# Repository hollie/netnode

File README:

This is the repository for the netnode project. 

WHAT IS THIS?
-------------

The netnode is an Ethernet-connected microcontroller. It is designed as a generic electronics platform that can be used to automate various tasks in and around the house.

The first version is built around a Microchip PIC microcontroller and a LanTronix XPORT serial to Ethernet convertor.

In this form, the netnode is running for over 5 years at our home. It is used to control electrical blinds, to measure temperatures in our HVAC system, to monitor our solar heating installation, to measure the output of a photovoltaic installation and to interface to wireless sensors.

The latest developments around the netnode focus on adding a standard interface for reporting sensors data and to control basic devices. The selected standard is xPL, because it allows coupling the netnode to a vast amount of existing software such as e.g. Misterhouse.

This repository is divided in three sections: 
 * hardware: the hardware design files of the netnode. The netnode is designed in Eagle and the design is open source (see license below).
 * firmware: the firmware for the controller on the netnode. Currently there is only a single subfolder here. All existing firmware is mapped on a netnode v1.x that is based on a Microchip PIC18F controller.
 * software: various host software packages used to interface to a netnode running a certain firmware. Most of the subfolders here implement a kind of datalogging functionality to RRD databases.
    
AUTHOR
------

Lieven Hollevoet designed the netnode at the time he was building his house. His goal was to build a low-energy home, and setting such a goal of course implies deploying a measurement network to check if the efforts were worthwhile. 
After experimenting with a CAN-based solution, he decided Ethernet was the way to go. The main reasons to go for Ethernet were that the cabling was already present, and that on the computer interface side Ethernet is an interface that is available on every computing device, opposed to CAN which isn't. 

CREDITS
-------

Some 'like-minded' people have contributed to the codebase. 

Dirk Buekenhoudt helped in coding and debugging the xPL interface code. He is currently working on adding digital inputs and outputs.

Roeland Vandebriel wrote the initial code for the SHT7x humidity sensors and is working on merging my Technische Alternative DL output interface code that I initially wrote for my TA UVR61-1. He is working on interfacing to the TA UVR1611.

DEMO
----

A demo of what measurements are done using netnode hardware can be found here:
http://lika.be/uushuus_stats/live.htm

LICENSE
-------

All work in this repository is available under the Creative Commons 
Attribution-NonCommercial-ShareAlike license 3.0.

http://creativecommons.org/licenses/by-nc-sa/3.0/

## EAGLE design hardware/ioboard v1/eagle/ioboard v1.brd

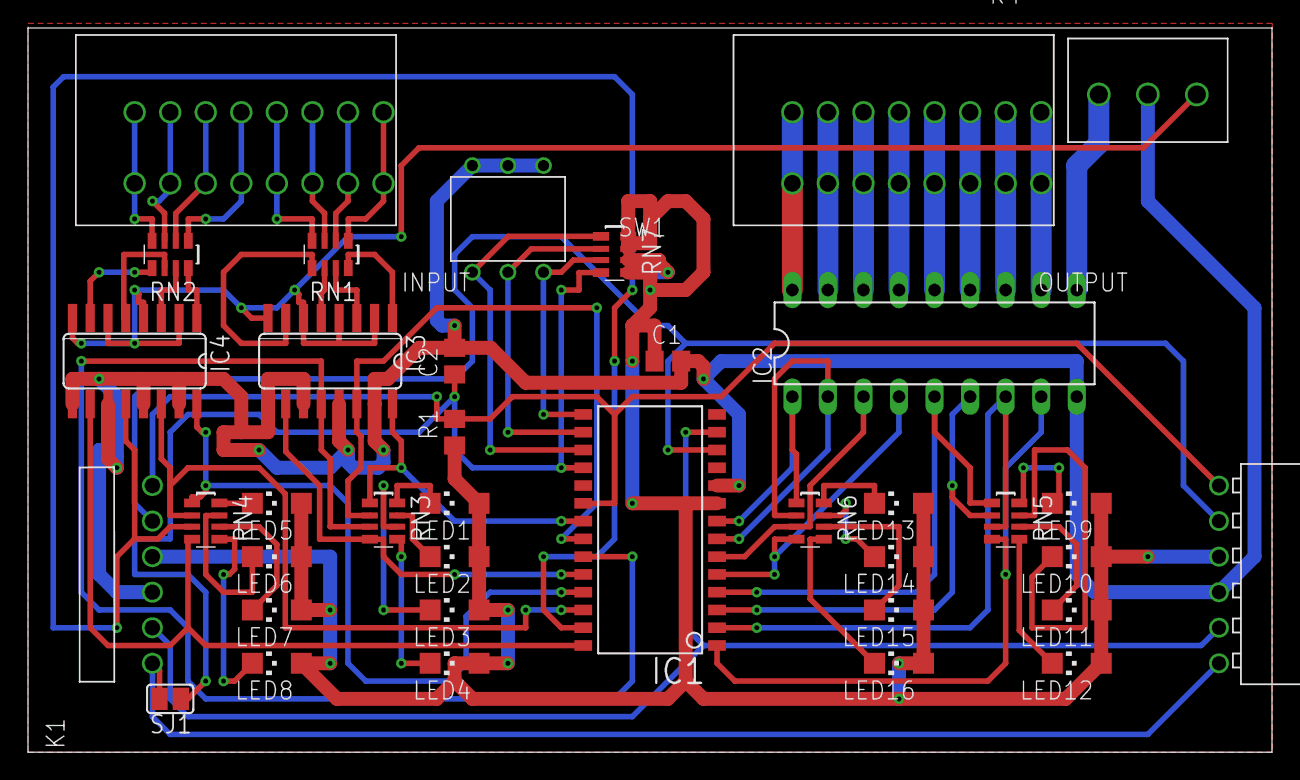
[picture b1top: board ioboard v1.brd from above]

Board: 2 copper layers, 88.9 x 51.7 mm, 37 parts (0 on the bottom side), 68 nets.

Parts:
C1, C2: C0805
IC1: MCP23017SO; SO28W
IC2: DIL18
IC3, IC4: ACPL-244; SO16
INPUT: 691402910008
K1: 61300611021
K2: 613006143121
K4: 691214110003
LED1, LED2, LED3, LED4, LED5, LED6, LED7, LED8, LED9, LED10, LED11, LED12, LED13, LED14, LED15, LED16: CHIPLED_1206
OUTPUT: 691402910008
R1: R0805
RN1, RN2, RN3, RN4, RN5, RN6, RN7: RN8P-4R-CRA06S
SJ1: SJ
SW1: 418127270903

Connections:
!RST: C2.1, IC1.18, RN7.4, SJ1.1
ADDR0: IC1.15, RN7.3, SW1.6
ADDR1: IC1.16, RN7.2, SW1.5
ADDR2: IC1.17, RN7.1, SW1.4
AGND: IC3.2, IC3.4, IC3.6, IC3.8, IC4.2, IC4.4, IC4.6, IC4.8, K4.3
GND: C1.2, C2.2, IC1.10, IC2.9, IC3.9, IC3.11, IC3.13, IC3.15, IC4.9, IC4.11, IC4.13, IC4.15, K1.4, K2.4, K4.2, SW1.1, SW1.2, SW1.3
IN0: INPUT.1, INPUT.16, RN1.1
IN1: INPUT.2, INPUT.15, RN1.2
IN2: INPUT.3, INPUT.14, RN1.3
IN3: INPUT.4, INPUT.13, RN1.4
IN4: INPUT.5, INPUT.12, RN2.1
IN5: INPUT.6, INPUT.11, RN2.2
IN6: INPUT.7, INPUT.10, RN2.3
IN7: INPUT.8, INPUT.9, RN2.4
INT: IC1.20, K1.1, K2.1, R1.2
IN_L0: IC1.21, IC3.16, RN3.1
IN_L1: IC1.22, IC3.14, RN3.2
IN_L2: IC1.23, IC3.12, RN3.3
IN_L3: IC1.24, IC3.10, RN3.4
IN_L4: IC1.25, IC4.16, RN4.1
IN_L5: IC1.26, IC4.14, RN4.2
IN_L6: IC1.27, IC4.12, RN4.3
IN_L7: IC1.28, IC4.10, RN4.4
unnamed: IC3.1, RN1.8
unnamed: IC3.3, RN1.7
unnamed: IC3.5, RN1.6
unnamed: IC3.7, RN1.5
unnamed: IC4.1, RN2.8
unnamed: IC4.3, RN2.7
unnamed: IC4.5, RN2.6
unnamed: IC4.7, RN2.5
unnamed: LED1.C, RN3.8
unnamed: LED2.C, RN3.7
unnamed: LED9.C, RN5.8
unnamed: LED10.C, RN5.7
unnamed: LED11.C, RN5.6
unnamed: LED12.C, RN5.5
unnamed: LED3.C, RN3.6
unnamed: LED4.C, RN3.5
unnamed: LED13.C, RN6.8
unnamed: LED14.C, RN6.7
unnamed: LED15.C, RN6.6
unnamed: LED16.C, RN6.5
unnamed: LED5.C, RN4.8
unnamed: LED6.C, RN4.7
unnamed: LED7.C, RN4.6
unnamed: LED8.C, RN4.5
OUT0: IC2.11, OUTPUT.1, OUTPUT.16
OUT1: IC2.12, OUTPUT.2, OUTPUT.15
OUT2: IC2.13, OUTPUT.3, OUTPUT.14
OUT3: IC2.14, OUTPUT.4, OUTPUT.13
OUT4: IC2.15, OUTPUT.5, OUTPUT.12
OUT5: IC2.16, OUTPUT.6, OUTPUT.11
OUT6: IC2.17, OUTPUT.7, OUTPUT.10
OUT7: IC2.18, OUTPUT.8, OUTPUT.9
OUT_L0: IC1.1, IC2.8, RN5.4
OUT_L1: IC1.2, IC2.7, RN5.3
OUT_L2: IC1.3, IC2.6, RN5.2
OUT_L3: IC1.4, IC2.5, RN5.1
OUT_L4: IC1.5, IC2.4, RN6.4
OUT_L5: IC1.6, IC2.3, RN6.3
OUT_L6: IC1.7, IC2.2, RN6.2
OUT_L7: IC1.8, IC2.1, RN6.1
RST_EXT: K1.6, K2.6, SJ1.2
SCL: IC1.12, K1.2, K2.2
SDA: IC1.13, K1.5, K2.5
V+: IC2.10, K4.1
VDD: C1.1, IC1.9, K1.3, K2.3, LED1.A, LED2.A, LED3.A, LED4.A, LED5.A, LED6.A, LED7.A, LED8.A, LED9.A, LED10.A, LED11.A, LED12.A, LED13.A, LED14.A, LED15.A, LED16.A, R1.1, RN7.5, RN7.6, RN7.7, RN7.8

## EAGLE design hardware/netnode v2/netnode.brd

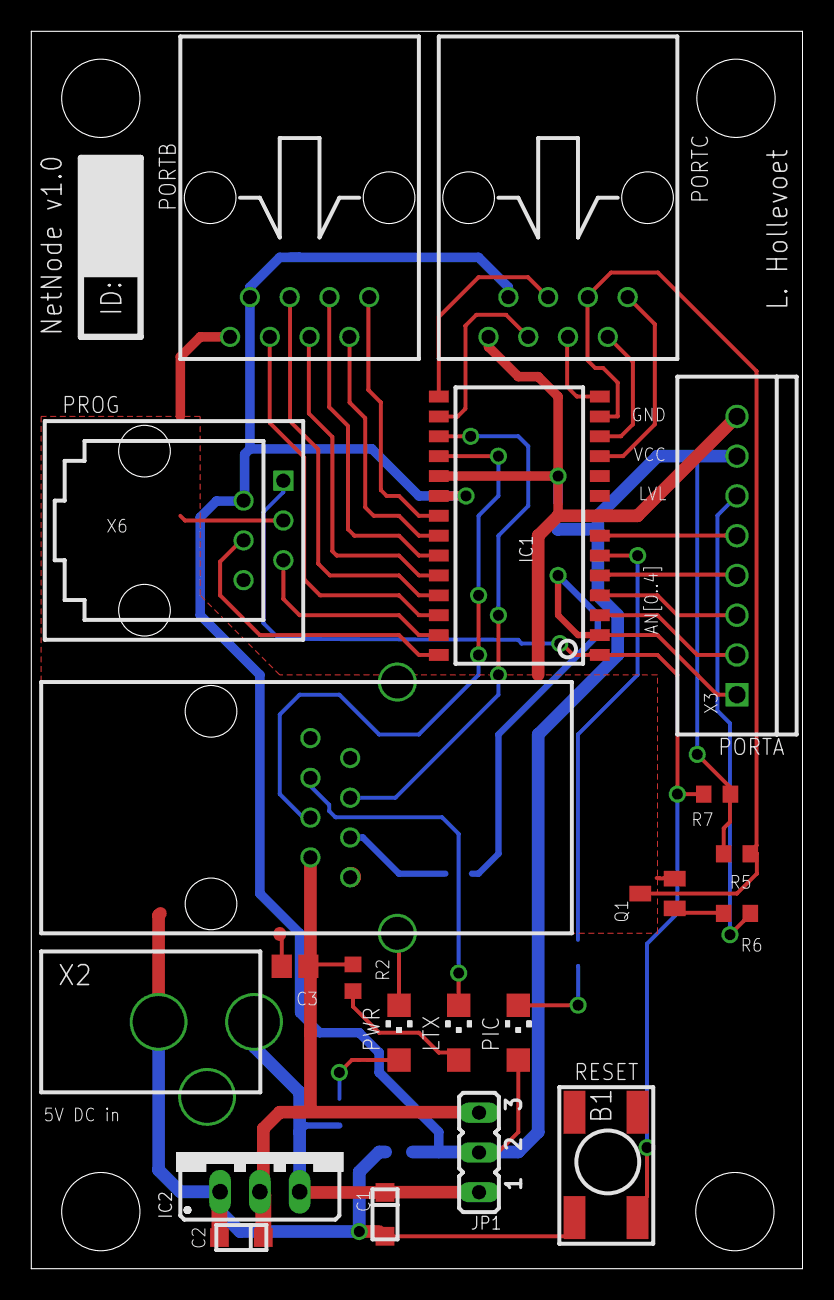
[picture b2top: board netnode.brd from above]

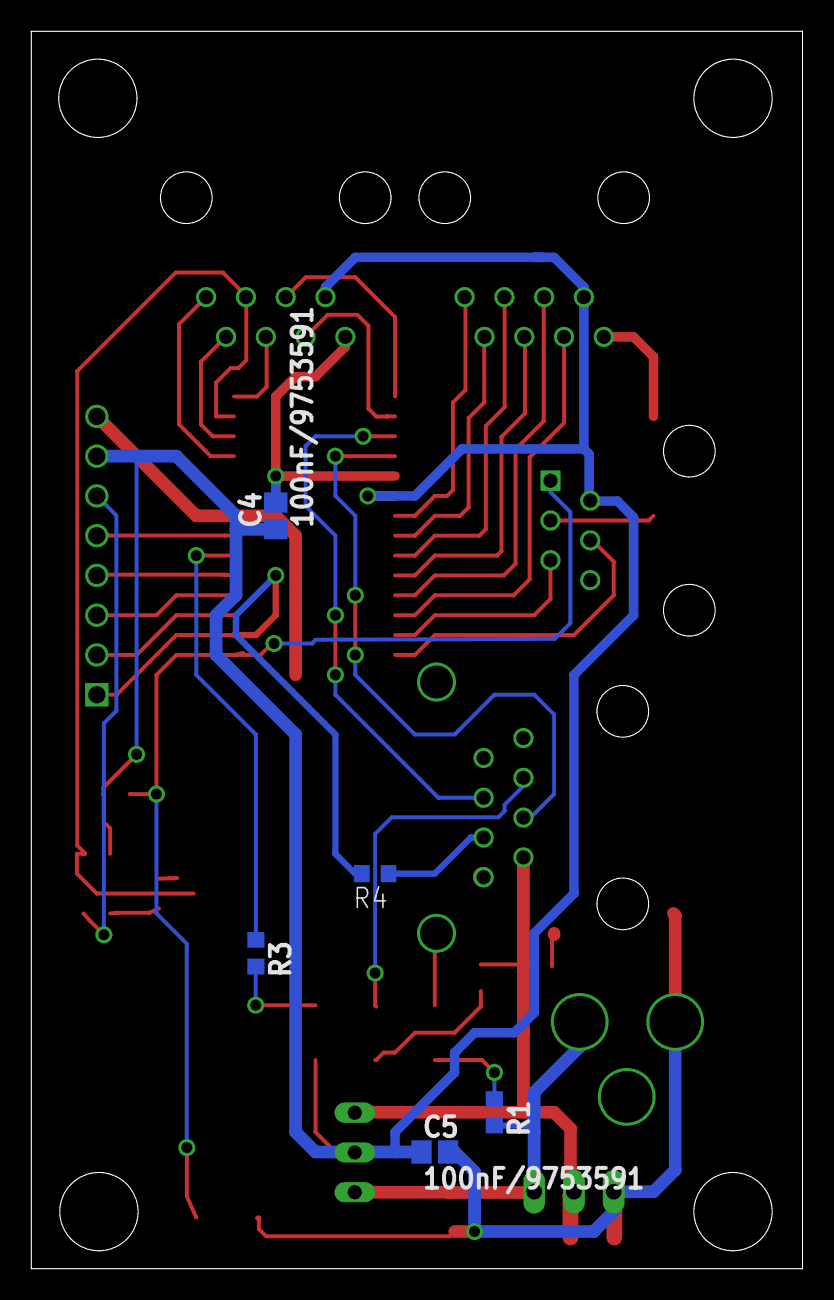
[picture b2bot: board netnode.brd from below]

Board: 4 copper layers, 49.3 x 79.0 mm, 26 parts (5 on the bottom side), 34 nets.

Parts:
B1: 9902031; PUSHBUTTON
C1, C2: 10u/7565127; CHIPCAP
C3, C4, C5: 100nF/9753591; C0805
IC1: PIC18F2320/9762051; SO-28W
IC2: 1087165; 78XXS
JP1: JP2
LTX: CHIPLED_1206
PIC: CHIPLED_1206
PWR: CHIPLED_1206
Q1: 1081235; SOT23
R1, R2, R3: R0603
R4: 0; R0603
R5: 10k/9331700; R0603
R6: 470k/612807RL; R0603
R7: 1k/9331697RL; R0603
X1: XPORT
X2: DC10R/224959; DC10R
X3: SCREW_TERMINAL/3041438; SCREW_TERMINAL_8PINS
X4, X5: RJ45H
X6: X/1097917; RJ11

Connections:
+3V3: C2.+, C3.1, IC2.GND, JP1.3, R2.2, X1.2
+5V: C1.+, IC2.OUT, JP1.1, R1.2, X2.1
AN0: IC1.2, R4.2, X3.1
AN1: IC1.3, X3.2
AN2: IC1.4, X3.3
AN3: IC1.5, X3.4
AN4: IC1.7, X3.5
CP1: LTX.C, X1.6
GND: B1.1, C1.-, C2.-, C3.2, C4.2, C5.2, IC1.8, IC1.19, IC2.IN, PWR.C, Q1.2, X1.1, X1.TAB1, X1.TAB2, X2.3, X3.8, X4.P$8, X5.P$8, X6.3
LVL: R6.2, X3.6
MCLR: B1.3, IC1.1, R7.2, X6.1
unnamed: Q1.1, R6.1
unnamed: PWR.A, R1.1
unnamed: R4.1, X1.3
unnamed: LTX.A, R2.1
PIC: PIC.C, R3.2
PIC_RX: IC1.18, X1.4
PIC_TX: IC1.17, X1.5
RA4: IC1.6, R3.1
RB0: IC1.21, X4.P$1
RB1: IC1.22, X4.P$2
RB2: IC1.23, X4.P$3
RB3: IC1.24, X4.P$4
RB4: IC1.25, X4.P$5
RB5: IC1.26, X4.P$6
RB6: IC1.27, X6.5
RB7: IC1.28, X6.4
RC0: IC1.11, X5.P$1
RC1: IC1.12, X5.P$2
RC2: IC1.13, Q1.3, R5.1, X5.P$3
RC3: IC1.14, X5.P$4
RC4: IC1.15, X5.P$5
RC5: IC1.16, X5.P$6
VCC: C4.1, C5.1, IC1.20, JP1.2, PIC.A, R5.2, R7.1, X3.7, X4.P$7, X5.P$7, X6.2

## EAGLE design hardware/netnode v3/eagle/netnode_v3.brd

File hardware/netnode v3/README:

Specifications of the Netnode v3
================================

Ethernet-connected PIC microcontroller

Highlights:
-----------
* Input voltage: 5 - 30 V, short circuit protected
* 10/100 Ethernet connection configurable through web interface on port 80
* System voltage: 3V3
* Can deliver up to 600 mA to target application.
* Typical power consumption: 0.92 W with ethernet running in normal performance mode
* 8-pin screw terminal connector with 4 GPIOs + ground connected to interrupt pins
* 8-pin screw terminal connector with I2C, 1 PWM, 1 optically isolated input, 1 one-wire bus, 3V3 and GND 
* 4 analog input pins broken out to non-populated header
* ICSP header on board
* Second serial port broken out to header to be able to easily connect XBee radio modules
* PIC has bootloader that allows firmware upgrades over the ethernet interface (*)
* optically isolated input designed for 12V input level (level can be changed by replacing a resistor)
* Open hardware, you're invited to thinker with it. 

Description:
------------
This is a PIC board that was developed to monitor the energy consumption and temperatures in and around our house. Multiple firmwares are available that can be loaded to have the board perform the functionality that is required.

Available firmwares are:
------------------------
 * one-wire to xPL bridge. Allows connecting one-wire temperature sensors, reports their status over xPL for easy integration with existing xPL software (e.g. Misterhouse). Plug the device in your network and the sensors appear in the software.
 * one-wire and SHTxx relative humidity to Cosm bridge. Idem as previous, but reports the sensor status to Cosm.com (previously Pachube). Ideal for people that don't have or want to keep a home server running to report sensor values to Cosm.
 * Technische Alternative solar heating controller interface (TA UVR61-3 and alike). Reports the status of your controller and the attached sensors over xPL (*).
 * TA to Cosm bridge. Idem as previous but reports to Cosm.com instead (*).

*: to be implemented

All work in this folder is available under the Creative Commons 
Attribution-NonCommercial-ShareAlike license 3.0.

http://creativecommons.org/licenses/by-nc-sa/3.0/

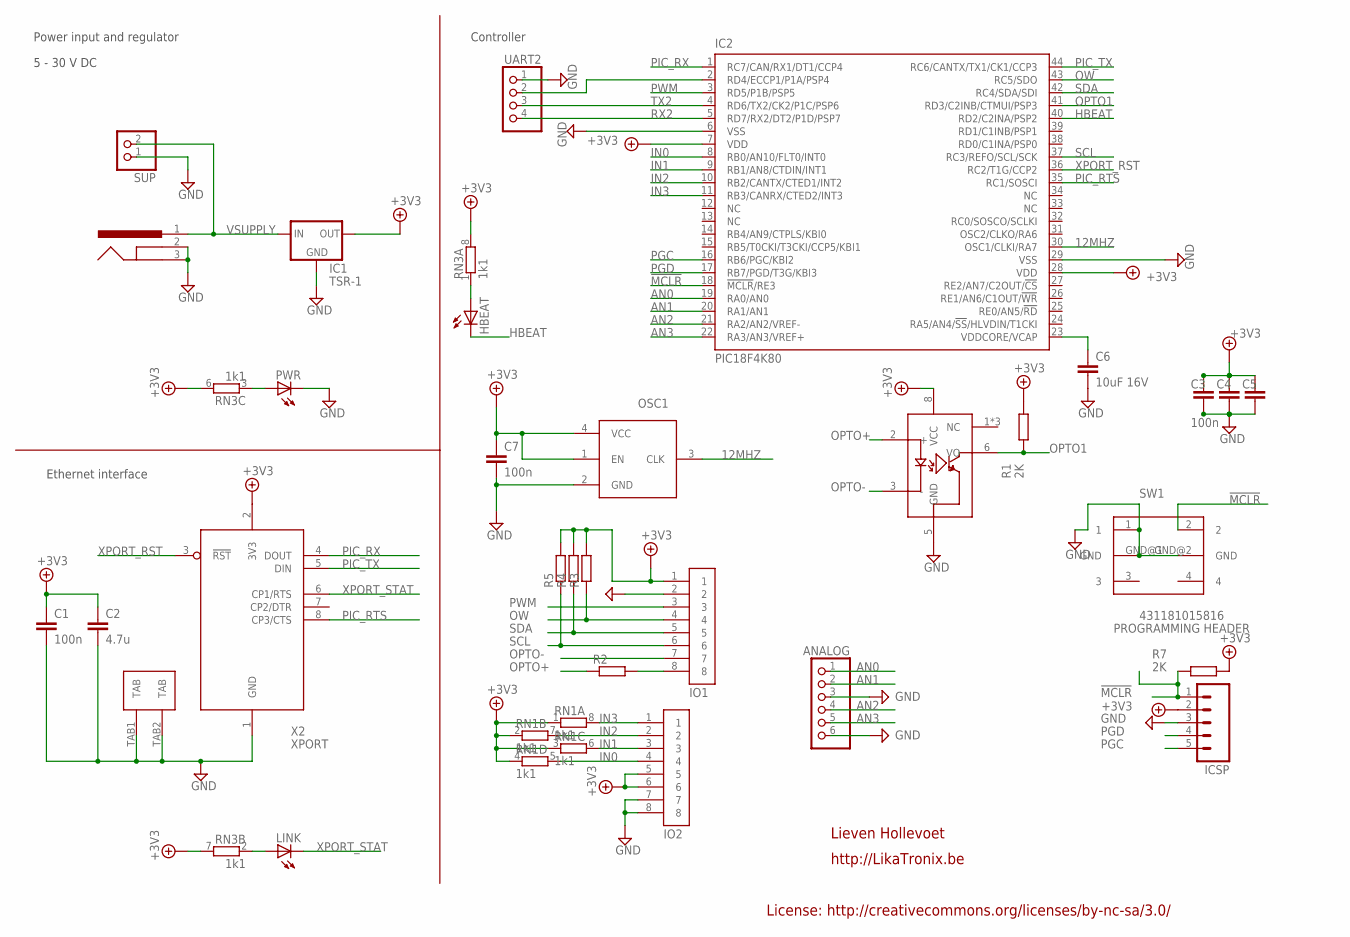
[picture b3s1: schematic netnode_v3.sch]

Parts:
ANALOG: PINHD-1X6; 1X06
C1, C3, C4, C5, C7: 100n; C0805; MPN 08055C104JAT2A
C2: 4.7u; C0805; MPN 0805YD475KAT2A
C6: 10uF 16V; C1206; MPN C1206C106K4PAC-TU
HBEAT: LEDCHIPLED_1206; CHIPLED_1206; MPN KP-3216EC
IC1: TSR-1; TSR1-SIPS; MPN TSR 1-2433
IC2: PIC18F4K80; TQFP44; MPN PIC18F45K80-I/PT
IC3: FOD060L; SO-08
ICSP: ICSP; 1X05
IO1, IO2: SCREW_TERMINAL; SCREW_TERMINAL_8PINS; MPN 1725711
LINK: LEDCHIPLED_1206; CHIPLED_1206; MPN KP-3216EC
OSC1: TXC - 7X-12.000MBB-T; 7W_7X5; MPN 7X-12.000MBB-T
PWR: LEDCHIPLED_1206; CHIPLED_1206; MPN KP-3216EC
R1, R7: 2K; R0805; MPN CR0603-FX-2001ELF
R2: R-EU_M0805; M0805
R3, R4, R5: R-EU_R0603; R0603
RN1, RN3: 1k1; RN8P-4R-CRA06S; MPN EXB38V102JV
SUP: PINHD-1X2; 1X02
SW1: 431181015816
UART2: PINHD-1X4; 1X04
X1: DC10R; MPN DC10A
X2: XPORT

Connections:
12MHZ: IC2.30 (OSC1/CLKI/RA7), OSC1.3 (CLK)
!MCLR: IC2.18 (!MCLR!/RE3), ICSP.1, R7.1, SW1.2
+3V3: C1.1, C2.1, C3.1, C4.1, C5.1, C7.1, IC1.3 (OUT), IC2.7 (VDD), IC2.28 (VDD), IC3.8 (VCC), ICSP.2, IO1.1, IO2.5, IO2.6, OSC1.1 (EN), OSC1.4 (VCC), R1.2, R3.2, R4.2, R5.2, R7.2, RN1.1, RN1.2 (1), RN1.3 (1), RN1.4 (1), RN3.6 (2), RN3.7 (2), RN3.8 (2), X2.2 (3V3)
AN0: ANALOG.1, IC2.19 (RA0/AN0)
AN1: ANALOG.2, IC2.20 (RA1/AN1)
AN2: ANALOG.4, IC2.21 (RA2/AN2/VREF-)
AN3: ANALOG.5, IC2.22 (RA3/AN3/VREF+)
GND: ANALOG.3, ANALOG.6, C1.2, C2.2, C3.2, C4.2, C5.2, C6.2, C7.2, IC1.2 (GND), IC2.6 (VSS), IC2.29 (VSS), IC3.5 (GND), ICSP.3, IO1.2, IO2.7, IO2.8, OSC1.2 (GND), PWR.C, SUP.1, SW1.1, SW1.GND@1 (GND), SW1.GND@2 (GND), UART2.1, X1.2 (CONTACT), X1.3 (SHIELD), X2.1 (GND), X2.TAB1 (TAB), X2.TAB2 (TAB)
HBEAT: HBEAT.C, IC2.40 (RD2/C2INA/PSP2)
IN0: IC2.8 (RB0/AN10/FLT0/INT0), IO2.4, RN1.5 (2)
IN1: IC2.9 (RB1/AN8/CTDIN/INT1), IO2.3, RN1.6 (2)
IN2: IC2.10 (RB2/CANTX/CTED1/INT2), IO2.2, RN1.7 (2)
IN3: IC2.11 (RB3/CANRX/CTED2/INT3), IO2.1, RN1.8 (2)
unnamed: LINK.A, RN3.2 (1)
unnamed: PWR.A, RN3.3 (1)
unnamed: HBEAT.A, RN3.1
OPTO1: IC2.41 (RD3/C2INB/CTMUI/PSP3), IC3.6 (VO), R1.1
OPTO+: IC3.2 (+), R2.1
OPTO+_PRE_RES: IO1.8, R2.2
OPTO-: IC3.3 (-), IO1.7
OW: IC2.43 (RC5/SDO), IO1.4, R3.1
PGC: IC2.16 (RB6/PGC/KBI2), ICSP.5
PGD: IC2.17 (RB7/PGD/T3G/KBI3), ICSP.4
PIC_RTS: IC2.35 (RC1/SOSCI), X2.8 (CP3/CTS)
PIC_RX: IC2.1 (RC7/CAN/RX1/DT1/CCP4), X2.4 (DOUT)
PIC_TX: IC2.44 (RC6/CANTX/TX1/CK1/CCP3), X2.5 (DIN)
PWM: IC2.3 (RD5/P1B/PSP5), IO1.3
RD4: IC2.2 (RD4/ECCP1/P1A/PSP4), UART2.2
RX2: IC2.5 (RD7/RX2/DT2/P1D/PSP7), UART2.4
SCL: IC2.37 (RC3/REFO/SCL/SCK), IO1.6, R5.1
SDA: IC2.42 (RC4/SDA/SDI), IO1.5, R4.1
TX2: IC2.4 (RD6/TX2/CK2/P1C/PSP6), UART2.3
VDDCAP: C6.1, IC2.23 (VDDCORE/VCAP)
VSUPPLY: IC1.1 (IN), SUP.2, X1.1 (CENTER)
XPORT_RST: IC2.36 (RC2/T1G/CCP2), X2.3 (!RST)
XPORT_STAT: LINK.C, X2.6 (CP1/RTS)

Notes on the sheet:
Power input and regulator
5 - 30 V DC
Ethernet interface
PROGRAMMING HEADER
Lieven Hollevoet
http://LikaTronix.be
License: http://creativecommons.org/licenses/by-nc-sa/3.0/
Controller

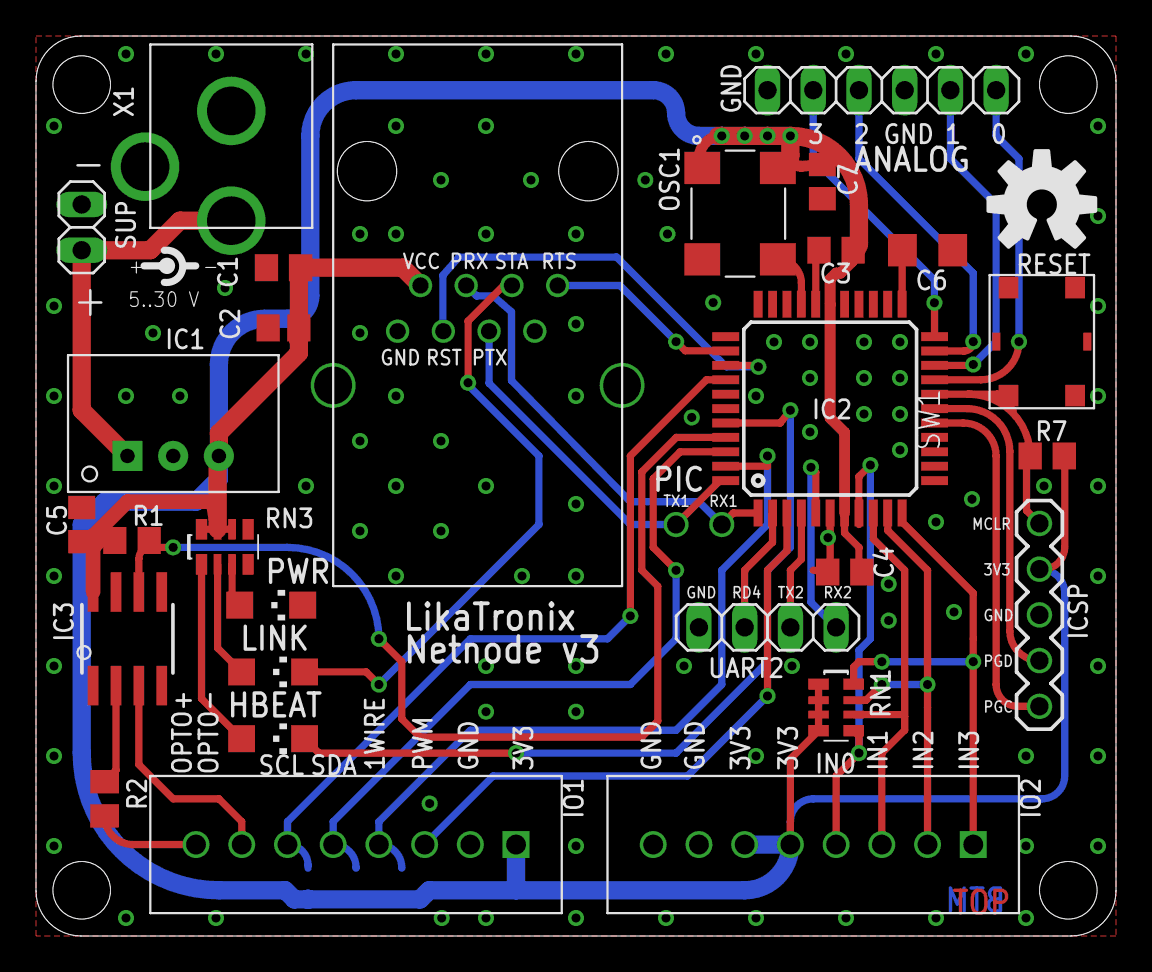
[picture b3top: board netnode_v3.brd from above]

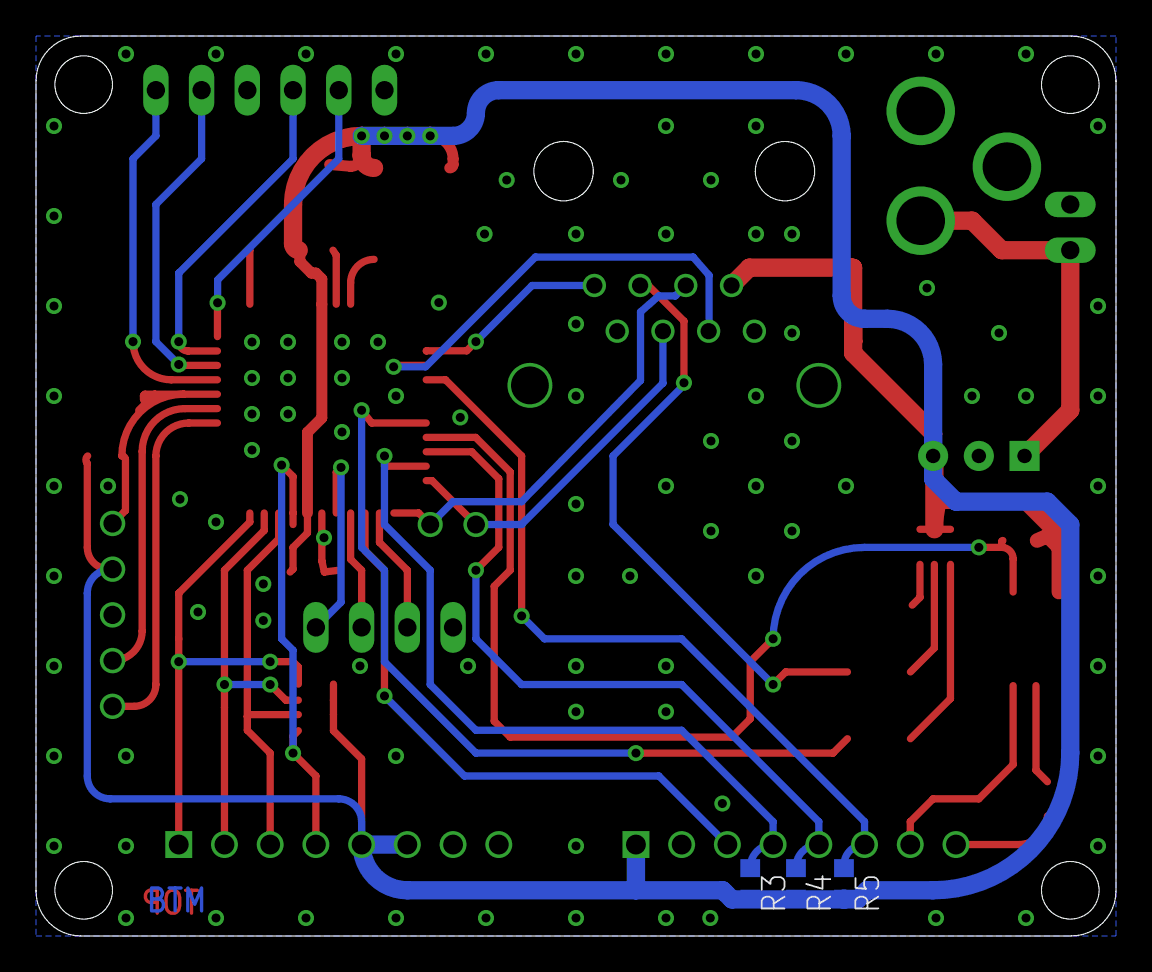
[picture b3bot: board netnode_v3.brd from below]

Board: 2 copper layers, 60.0 x 50.0 mm, 31 parts (3 on the bottom side), 36 nets.

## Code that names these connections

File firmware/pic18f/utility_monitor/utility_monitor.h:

/*************************************************************
* Utility meter monitor
*
* (c) 2009, Lieven Hollevoet.
**************************************************************
* compiler        : Microchip C18 v3.40
* target device   : PIC18F2520/PIC18F2580
* clockfreq       : 8 MHz (internal oscillator)
* target hardware : NetNode
* UART speed      : 38400 bps
*************************************************************/
#ifndef _UTILMONI_H_
#define _UTILMONI_H_

// Define port directions, 1=input
#define PortAConfig  	0xFF
#define PortBConfig  	0x0F
#define PortCConfig  	0xBB
#define PortDConfig     0xF0

// Define bit variables attached to pins
#ifdef __18F45K80_H

#define stat0    (PORTDbits.RD2)
#define xport_rst (PORTCbits.RC2)
#define xport_cts (PORTCbits.RC1)

// Timer values
#define TMR0_VALUE 0x0BDB // For a second interrupt runnning @ 64 MHz with 256 prescaler
#define TMR1_VALUE 0xB1E0 // For 20 ms interrupt.

/* TODO fix the timer values */

#else

#define stat0    (PORTAbits.RA4)

// Timer values
#define TMR0_VALUE 0x85EE // For a second interrupt.
#define TMR1_VALUE 0xB1E0 // For 20 ms interrupt.

#endif

#define show_hbeat() (blink_hbeat += 5);

// Function declarations
void init(void);
void high_isr(void);
void low_isr(void);


#endif //_UTILMONI_H_

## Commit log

2012-03-10 Added firmware for utility monitor
2012-03-10 Updated formatting of the README
2012-03-10 Fixed the compiler warnings caused by different compilation options of the libs vs the code
2012-03-10 Removed error files
2012-03-14 Added support for Sensirion SHTxx humidity sensors.
    Initial support for the sensors is added based on the code migrated by
    Roeland from my PSOC library.
    The readout is working and was reported through a non-standard xPL
    message.
    To be done: add xPL message support conform the specification.
    Bumped the firmware version to v4.6
2012-03-14 Started adding xPL compliant support for the SHT sensor
    Prepared the xPL lib for regularly polling the SHT sensor and to sense
    out xpl-trig messages when the reading changed.
    Bugfix: xpl_node_configuration was mistakingly reset completely in the
    init_instance_id function.
2012-03-15 Added reporting of the SHT sensor readings to the xPL library
2012-03-15 SHT sensor reporting tested on hardware
2012-03-21 Typo fix in README
2012-04-15 Added debug server script
2012-04-15 Added test client, updates test server
2012-04-15 Made client resemble curl.
2012-04-15 Oops, TCP packet should end with \r\n\r\n
2012-05-05 Updated test server for socket client testing
2012-05-05 Added first firmware for the Cosm interface
2012-05-06 Added description.
2012-05-06 Added project description and license.
2012-05-11 Correct calculation of whole and part value's
    For negative numbers the value_whole and value_part where not
    calculated correctly.
2012-05-11 Corrections for the decimals
    If the decimals where 09 or 0 something they where displayed without
    the 0
2012-05-11 correct the caluculation of value_whole and value_part for negative values
2012-05-12 Revert "correct the caluculation of value_whole and value_part for negative values"
    This reverts commit 01e6d6504f04271bffc7768f77fabc0a21840e01.
2012-05-12 - Move FeedNr to gateway - An other fix for negative temp values, when the value < 0 and > -1 eg -0,92 the - sign disapear because -0 does not exist.
2012-05-15 Implement multisensor code
2012-05-15 Added feed id to init function, bug fixed printing of scaled negative values.
2012-05-15 Updated gitignore and fixed a potential case where we miss the reporting condition due to condition not matching (unlikely, but better to be safe than to be sorry).
2012-06-11 Intermediate release, schematic to be completed.
2012-06-11 Backported bugfix fro Roeland
2012-06-15 Pre-final board files, silkscreen to be fixed
2012-06-17 Typo fix
2012-07-09 Further finalization of board
2012-07-09 Added project description
2012-07-16 Completed order codes.
2012-07-16 Added resistors and cleaned silkscreen
2012-07-16 Updated gitignore file to omit object files
2012-07-16 New firmware for PV reporting to Cosm
    Still in alpha phase, to be testen on hardware.
2012-07-16 Added changes to MPlab X files of the libs
2012-07-16 Changes to MPLab X files (new build platform)
2012-07-19 Further board cleanup
    * Silkscreen fixes + size increased
    * Replaced 0603 componentsn with 0805 counterparts for easier soldering
2012-07-19 Intermediate checkin, code to be tested
    In the process of moving the settings to EEPROM
2012-11-03 Added reset button.
    The reset button from Wuerth is a handy addition when developing firmware.
2012-11-11 Final fixes for boardout.
    Added decoupling caps, fixed silkscreen, reviewed compontents
2012-11-11 Added gerbers.
2012-11-11 Final gerber file commit of files sent to production. Fixed problems detected by PCB visualizer.
2012-11-11 Added historical versions of netnode for completeness, added initial version of inboard.
2012-11-14 Intermediate commit of ioboard.
2012-11-17 Updated IOboard with some more connectors and LEDs
2012-11-18 First board layout
2012-11-18 First routing attempt aith autorouter
    But no rules, just to know the routing is possible
2013-01-29 Initial support for v3 hardware
2013-01-30 Ordernumbers completed
2013-02-11 Initial xPL firmware up and running on netnode v3
2013-06-23 Netnode v3 is now reliably working as meter monitor running at 64 MHz.

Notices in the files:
parts and their libraries:
Wuerth_Elektronik_eiCan_01_Pin__Socked_H: Copyright: Würth Elektronik
